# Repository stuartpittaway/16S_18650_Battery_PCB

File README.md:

# 16S_18650_Battery_PCB
16S 18650 Battery PCB with balance leads - for testing BMS systems

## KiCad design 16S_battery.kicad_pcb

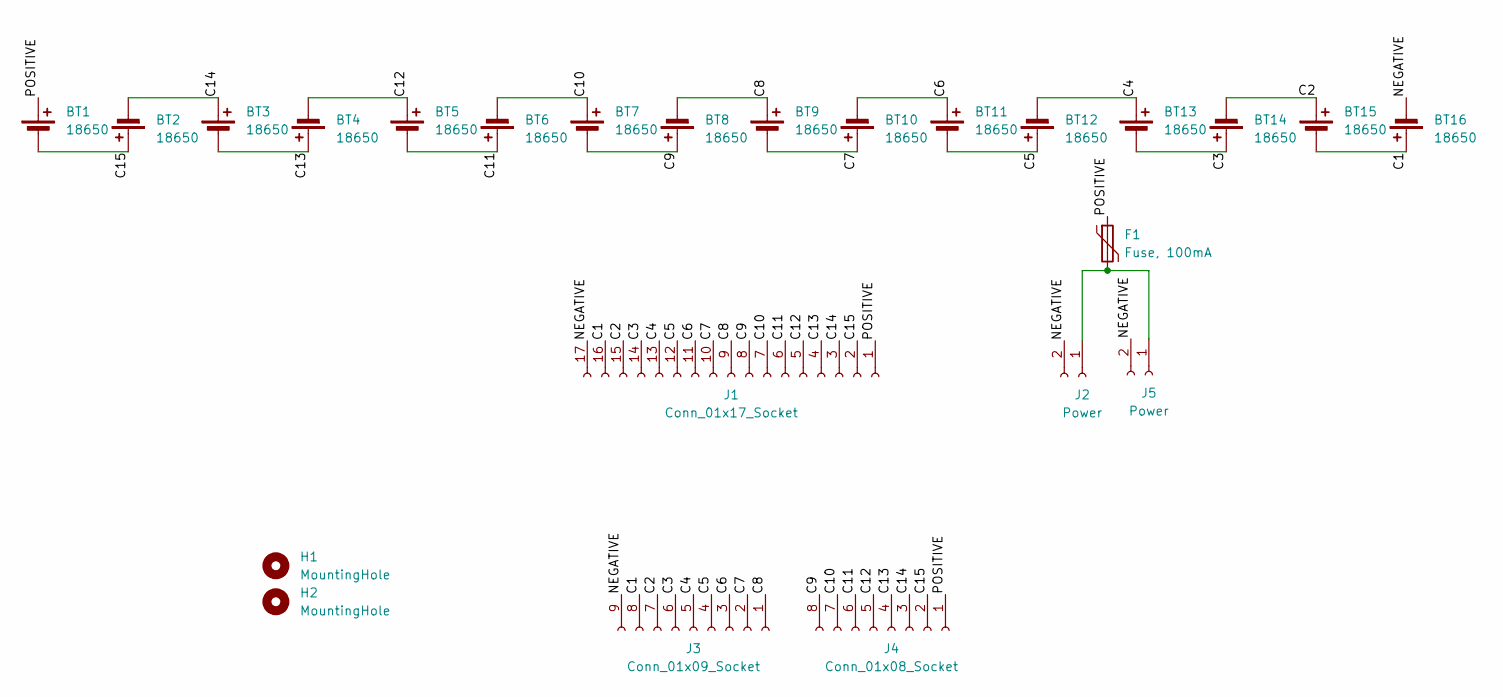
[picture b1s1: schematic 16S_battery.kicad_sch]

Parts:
BT1, BT2, BT3, BT4, BT5, BT6, BT7, BT8, BT9, BT10, BT11, BT12, BT13, BT14, BT15, BT16: 18650; MY-18650-01
F1: Fuse, 100mA; Fuse_Bourns_MF-RHT100; PartNumber JK250-100U; LCSCStockCode C2680606
H1, H2: MountingHole; MountingHole_3.5mm
J1: Conn_01x17_Socket; WJ15EDGRC-3.81-17P; PartNumber WJ15EDGRC-3.81-17P; LCSCStockCode C489980
J2, J5: Power; PhoenixContact_MC_1,5_2-G-3.81_1x02_P3.81mm_Horizontal; PartNumber WJ15EDGRC-3.81-2P; LCSCStockCode C8387
J3: Conn_01x09_Socket; JST_VH_B9P-VH_1x09_P3.96mm_Vertical; PartNumber B9P-VH(LF)(SN); LCSCStockCode C160321
J4: Conn_01x08_Socket; JST_VH_B8P-VH_1x08_P3.96mm_Vertical; PartNumber B8P-VH(LF)(SN); LCSCStockCode C160320

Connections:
/C1: BT15.2 (-), BT16.1 (+), J1.16, J3.8
/C2: BT14.2 (-), BT15.1 (+), J1.15, J3.7
/C3: BT13.2 (-), BT14.1 (+), J1.14, J3.6
/C4: BT12.2 (-), BT13.1 (+), J1.13, J3.5
/C5: BT11.2 (-), BT12.1 (+), J1.12, J3.4
/C6: BT10.2 (-), BT11.1 (+), J1.11, J3.3
/C7: BT9.2 (-), BT10.1 (+), J1.10, J3.2
/C8: BT8.2 (-), BT9.1 (+), J1.9, J3.1
/C9: BT7.2 (-), BT8.1 (+), J1.8, J4.8
/C10: BT6.2 (-), BT7.1 (+), J1.7, J4.7
/C11: BT5.2 (-), BT6.1 (+), J1.6, J4.6
/C12: BT4.2 (-), BT5.1 (+), J1.5, J4.5
/C13: BT3.2 (-), BT4.1 (+), J1.4, J4.4
/C14: BT2.2 (-), BT3.1 (+), J1.3, J4.3
/C15: BT1.2 (-), BT2.1 (+), J1.2, J4.2
/NEGATIVE: BT16.2 (-), J1.17, J2.2, J3.9, J5.2
/POSITIVE: BT1.1 (+), F1.1, J1.1, J4.1
unnamed: F1.2, J2.1, J5.1

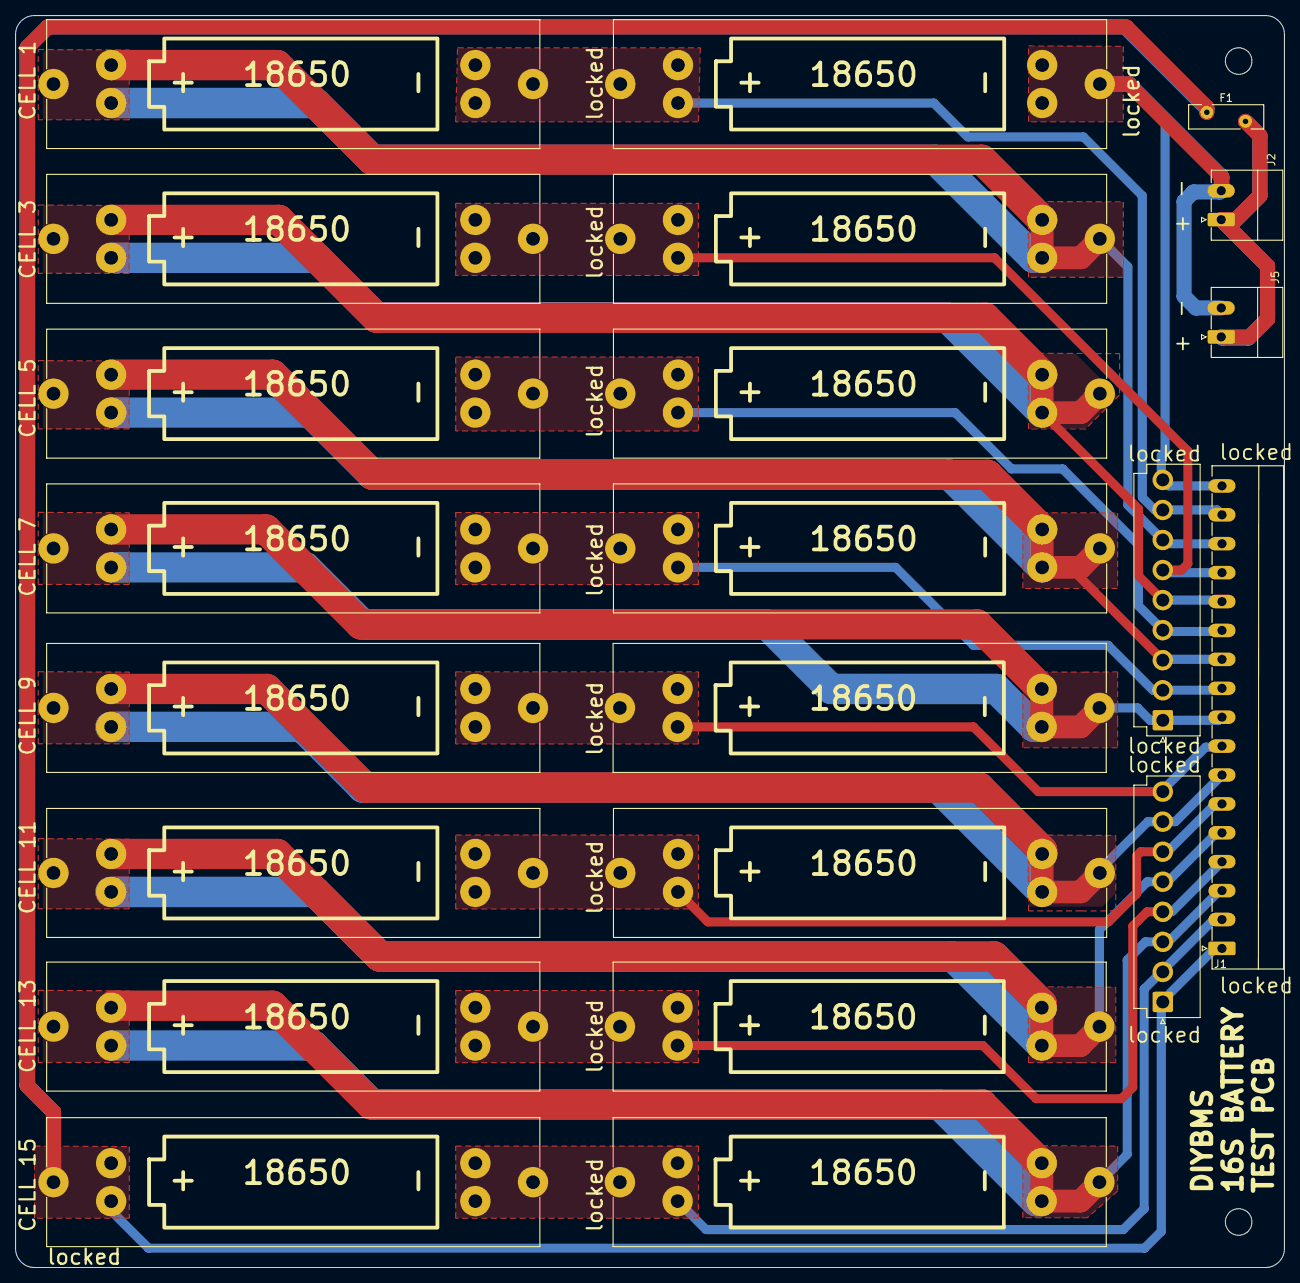
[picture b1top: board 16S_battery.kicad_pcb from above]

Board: 2 copper layers, 167.2 x 165.0 mm, 24 parts (0 on the bottom side), 18 nets.

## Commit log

2023-11-13 Initial check in
